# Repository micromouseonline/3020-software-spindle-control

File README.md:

# 3020 SOFTWARE SPINDLE CONTROL

Thanks to [Johnny](https://hackaday.io/Johnny) from [hackaday.io](http://hackaday.io) for his [fantastic work](https://hackaday.io/project/6776-3040-cnc-milling-machine-mods/log/21618-jp-1482-spindle-controller-schematic) reverse-engineering the JP-1481 spindle board, seen below:

### Problem

**You cannot control the spindle speed by any means other than the front panel knob.**

This is particularly important in an emergency stop situation.  While your controller will the stepper movement, the spindle will continue to spin.

The main interface (JP-382C) board routes pin 17 of the parallel port directly to the (unpopulated) "PWM OUT" connector on that board.  

The JP-1482 (spindle control) board has a PWM input, but the firmware on the STC15W408AS (the MCU that ultimately controls spindle speed) _does not_ respond to that input.  

### Solution

The solution is to use another MCU that reads from the existing front-panel knob, and the PWM from the interface board, that then simulates the front panel knob (using a programmable potentiometer).

The goal is to have a board you can simply plug in, and it _just works_.™

### Implementation

For the sake of ease, and getting up-and-running quickly, I opted to use an Arduino Pro Micro (5V), which I happened to have on hand.

The input PWM is buffered through a 6N136 opto isolator (since the PWM power supply is floating), and fed directly into the Arudino.

For output, there is an MCP41010 digital potentiometer, controlled via SPI. Since the front panel pot is 5K, we're only going to use ½ of it's 10K range.

Power (5v) is provided by the PWM board.

The software is standard Arduino code, though I'm using PlatformIO CLI since I'm not a big fan the Arduino IDE.  Why not bare metal AVR? This isn't a demanding application, and while the Arduino ecosystem isn't the most efficient, it does make it quick and easy to get things up-and-running.

### Construction

##### Schematic

##### BOM

| Ref   | P/N       |
|-------|-----------|
| P1    | B2B-XH-A(LF)(SN)|
| P2, P4| B3B-XH-A(LF)(SN) |
| P3    | B8B-XH-A(LF)(SN) |
| R1    | Any 0802 330 ohm SMT resistor|
| R2    | Any 0802 2200 ohm SMT resistor |
| D1    | 1N4148 (optional)|
| U1    | 6N136, 8 DIP |
| U2    | Arduino Pro Micro (Ebay clone) |
| U3    | MCP41010, 8 DIP |

The connectors on the board are compatible with the connectors on the JP-1482; they're the JST XH series. Be careful buying random "XH" connectors from Ebay or even Amazon, for two reasons:

1. The connectors are often 2.54mm pitch, instead of 2.50mm (XH is 2.50mm).  This will mostly work, but for the 8-pin connector, you're going to bend the pins of your board connector by doing this.
1. Make sure the cables you use are the "straight through" type -- pin 1 on one end goes to pin 1 on the other end.

Buy genuine XH connectors and cables from a reputable supplier (e.g. Digi-key).

The board layout is rather tight.  It's designed to have U1 and U3 soldered directly to the board, while U2 is in a socket, for ease of swapping, above the other ICs.

#### Compiling and installing firmware from source

###### Step 1:
[Install Platformio](http://docs.platformio.org/en/latest/installation.html)

###### Step 2

You may need to add the `--upload-port` parameter, depending on how your system enumerates the Arduino port.

```bash
cd 3020-software-spindle-control/fw
platformio run -t upload
```

#### Installing from pre-compiled `.hex` file

--- nothing here yet ---

#### Behavior

The code will measure the input PWM from your controller, and monitors the front panel spindle control knob.  The front panel knob sets the _maximum_ speed.  If this knob is at zero, the spindle will not be enabled.  Example: if the knob is at the 60% position, and you command a 30% spindle speed via PWM, then the output speed will be 18% (0.3 x 0.6) of spindle absolute maximum speed. Also, the spindle on/off switch overrides everything else when in the off position.

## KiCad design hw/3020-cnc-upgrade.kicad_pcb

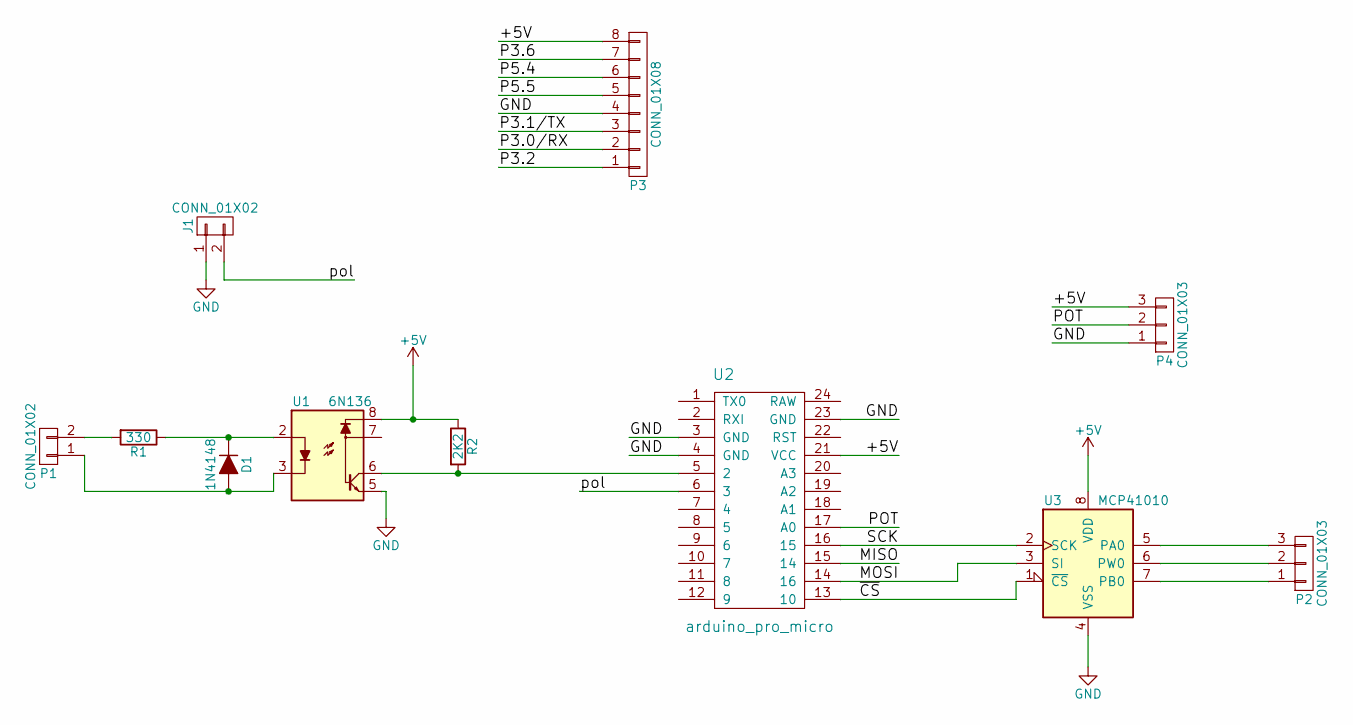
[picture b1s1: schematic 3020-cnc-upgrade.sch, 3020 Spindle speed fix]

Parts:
D1: 1N4148; SOD-123
J1: CONN_01X02; Pin_Header_Straight_1x02_Pitch2.54mm
P1: CONN_01X02; JST_XH_B02B-XH-A_02x2.50mm_Straight
P2, P4: CONN_01X03; JST_XH_B03B-XH-A_03x2.50mm_Straight
P3: CONN_01X08; JST_XH_B08B-XH-A_08x2.50mm_Straight
R1: 330; R_0805
R2: 2K2; R_0805
U1: 6N136; DIP-8_W7.62mm
U2: arduino_pro_micro; DIP-24_W15.24mm
U3: MCP41010; DIP-8_W7.62mm

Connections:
+5V: P3.8, P4.3, R2.1, U1.8, U2.21 (VCC), U3.8 (VDD)
/MISO: U2.15 (14)
/MOSI: U2.14 (16), U3.3 (SI)
/P3.0/RX: P3.2
/P3.1/TX: P3.3
/P3.2: P3.1
/P3.6: P3.7
/P5.4: P3.6
/P5.5: P3.5
/POT: P4.2, U2.17 (A0)
/SCK: U2.16 (15), U3.2 (SCK)
/pol: J1.2, U2.6 (3)
/~CS: U2.13 (10), U3.1 (~CS)
GND: J1.1, P3.4, P4.1, U1.5, U2.3 (GND), U2.4 (GND), U2.23 (GND), U3.4 (VSS)
unnamed: D1.1 (K), R1.1, U1.2
unnamed: D1.2 (A), P1.1, U1.3
unnamed: P1.2, R1.2
unnamed: P2.1, U3.7 (PB0)
unnamed: P2.2, U3.6 (PW0)
unnamed: P2.3, U3.5 (PA0)
unnamed: R2.2, U1.6, U2.5 (2)

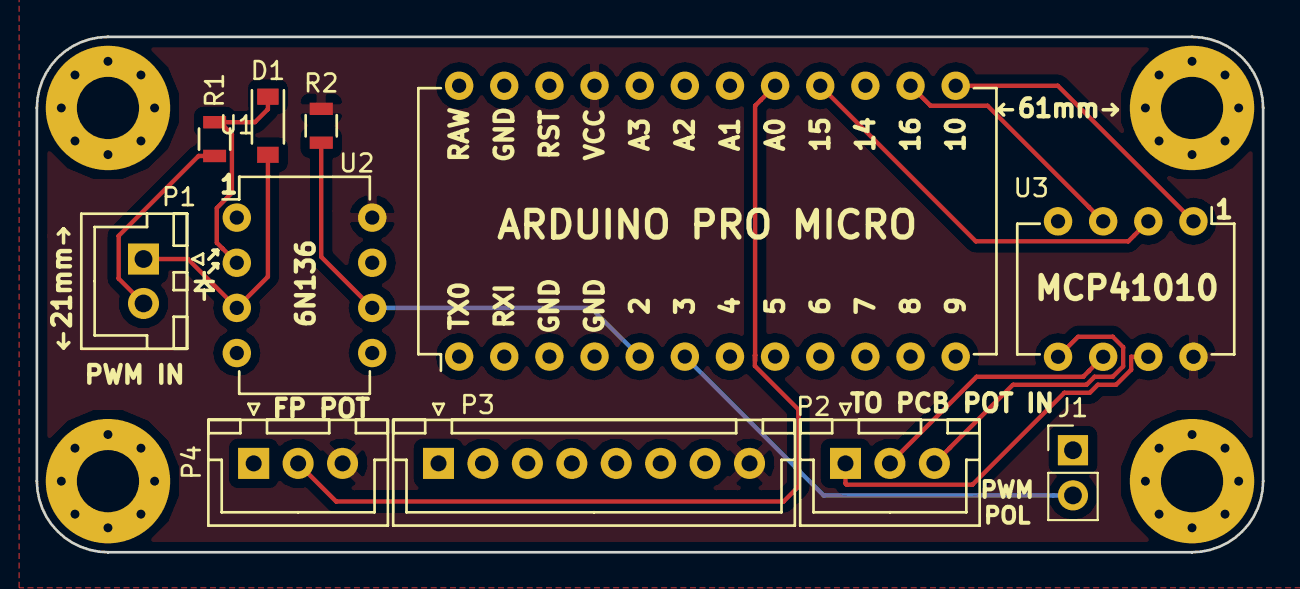
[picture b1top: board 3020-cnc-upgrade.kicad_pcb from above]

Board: 2 copper layers, 69.0 x 29.0 mm, 11 parts (0 on the bottom side), 14 nets.

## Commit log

2018-02-01 pcb and schem initial commit
2018-02-06 updated gitignore
2018-02-06 added needed .lib files
2018-02-10 pcb layout
2018-02-10 updates to layout
2018-02-13 added readme
2018-02-13 added img dir
2018-02-13 minor updates to hw
2018-02-13 minor readme update
2018-02-21 hardware updates
2018-03-07 swapped pins on pwm input
2018-03-13 updates to board and schematic
2018-03-13 added pot input, digipot output
2018-03-13 added URL and revision to board
2018-03-14 modified how inputs are handled
2018-03-14 added schematic image
2018-03-14 minor PCB tweak
2018-03-26 made debug printing optional
2018-03-27 added jumper to reverse spindle polarity
2018-03-27 added LED for debugging, and polarity inversion
